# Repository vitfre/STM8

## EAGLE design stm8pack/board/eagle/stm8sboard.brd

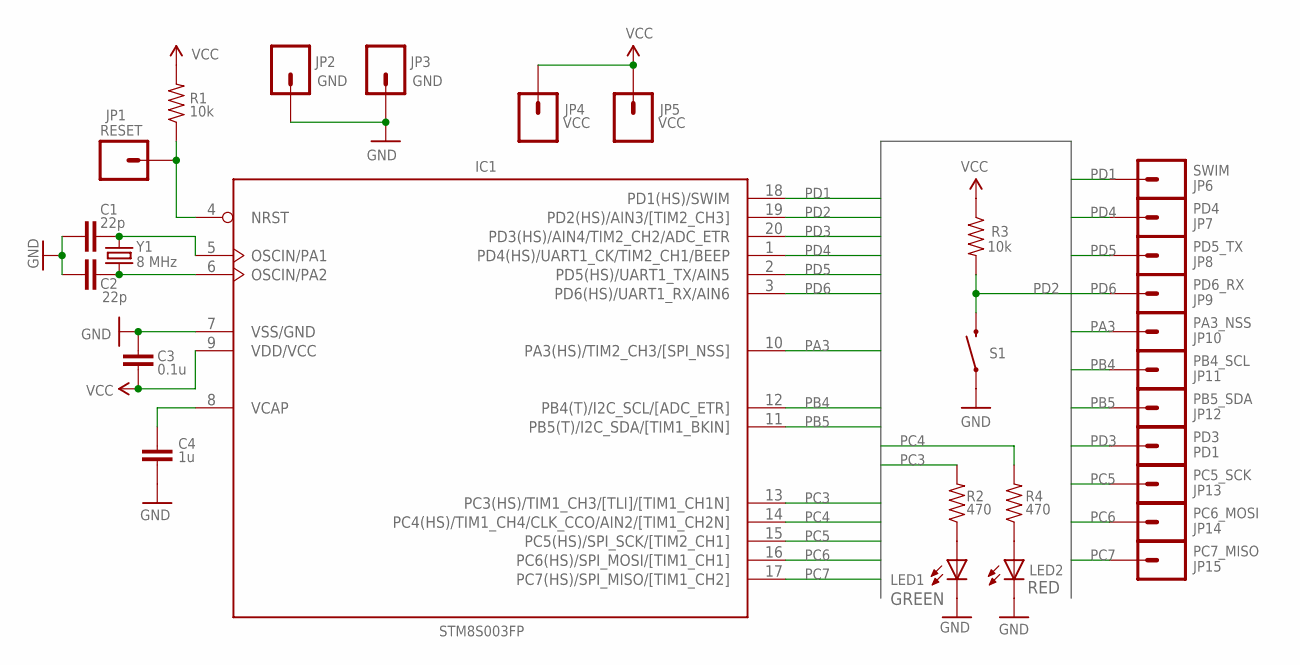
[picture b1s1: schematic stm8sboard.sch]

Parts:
C1, C2: 22p; 0805
C3: 0.1u; 0603-CAP
C4: 1u; 0603-CAP
IC1: STM8S003FP; TSSOP20
JP1: RESET; 1X01
JP2, JP3: GND; 1X01
JP4, JP5: VCC; 1X01
JP6: SWIM; 1X01
JP7: PD4; 1X01
JP8: PD5_TX; 1X01
JP9: PD6_RX; 1X01
JP10: PA3_NSS; 1X01
JP11: PB4_SCL; 1X01
JP12: PB5_SDA; 1X01
JP13: PC5_SCK; 1X01
JP14: PC6_MOSI; 1X01
JP15: PC7_MISO; 1X01
LED1: GREEN; LED-0603
LED2: RED; LED-0603
PD1: PD3; 1X01
R1, R3: 10k; 0805
R2, R4: 470; 0805
S1: SW; REED_SWITCH_PLASTIC
Y1: 8 MHz; HC49U-V

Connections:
GND: C1.1, C2.1, C3.1, C4.2, IC1.7 (VSS/GND), JP2.1, JP3.1, LED1.C, LED2.C, S1.P$1 (1)
unnamed: LED1.A, R2.1
unnamed: LED2.A, R4.1
unnamed: C2.2, IC1.6 (OSCIN/PA2), Y1.1
unnamed: C1.2, IC1.5 (OSCIN/PA1), Y1.2
unnamed: C4.1, IC1.8 (VCAP)
unnamed: IC1.4 (NRST), JP1.1, R1.1
PA3: IC1.10 (PA3(HS)/TIM2_CH3/[SPI_NSS]), JP10.1
PB4: IC1.12 (PB4(T)/I2C_SCL/[ADC_ETR]), JP11.1
PB5: IC1.11 (PB5(T)/I2C_SDA/[TIM1_BKIN]), JP12.1
PC3: IC1.13 (PC3(HS)/TIM1_CH3/[TLI]/[TIM1_CH1N]), R2.2
PC4: IC1.14 (PC4(HS)/TIM1_CH4/CLK_CCO/AIN2/[TIM1_CH2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), R4.2
PC5: IC1.15 (PC5(HS)/SPI_SCK/[TIM2_CH1]), JP13.1
PC6: IC1.16 (PC6(HS)/SPI_MOSI/[TIM1_CH1]), JP14.1
PC7: IC1.17 (PC7(HS)/SPI_MISO/[TIM1_CH2]), JP15.1
PD1: IC1.18 (PD1(HS)/SWIM), JP6.1
PD2: IC1.19 (PD2(HS)/AIN3/[TIM2_CH3]), R3.2, S1.P$2 (2)
PD3: IC1.20 (PD3(HS)/AIN4/TIM2_CH2/ADC_ETR), PD1.1
PD4: IC1.1 (PD4(HS)/UART1_CK/TIM2_CH1/BEEP), JP7.1
PD5: IC1.2 (PD5(HS)/UART1_TX/AIN5), JP8.1
PD6: IC1.3 (PD6(HS)/UART1_RX/AIN6), JP9.1
VCC: C3.2, IC1.9 (VDD/VCC), JP4.1, JP5.1, R1.2, R3.1

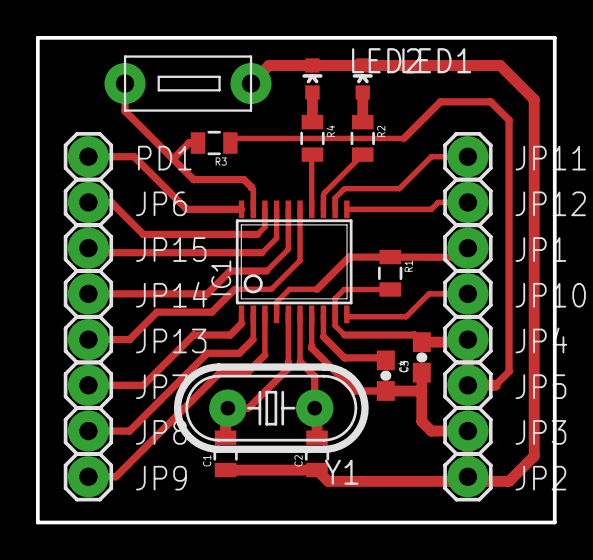
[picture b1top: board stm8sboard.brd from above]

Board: 2 copper layers, 28.7 x 26.9 mm, 29 parts (0 on the bottom side), 22 nets.

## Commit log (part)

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2015-09-20 :lollipop: Added .gitattributes & .gitignore files
2015-09-20 ADD test prj
2015-09-20 Add 4-UART
2015-10-04 Add stm8pack

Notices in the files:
parts and their libraries:
SparkFun: Licensing: CC v3.0 Share-Alike You are welcome to use this library for commercial purposes.
